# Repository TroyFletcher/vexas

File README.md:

# vexas
Vexas is a touch-type-able hardware keyboard offline Personal Organizer with a Vim-style interface, and serial support. Designed for rapid data input, data independence/security, and alarms that can be passive, persistent, or aggressive.

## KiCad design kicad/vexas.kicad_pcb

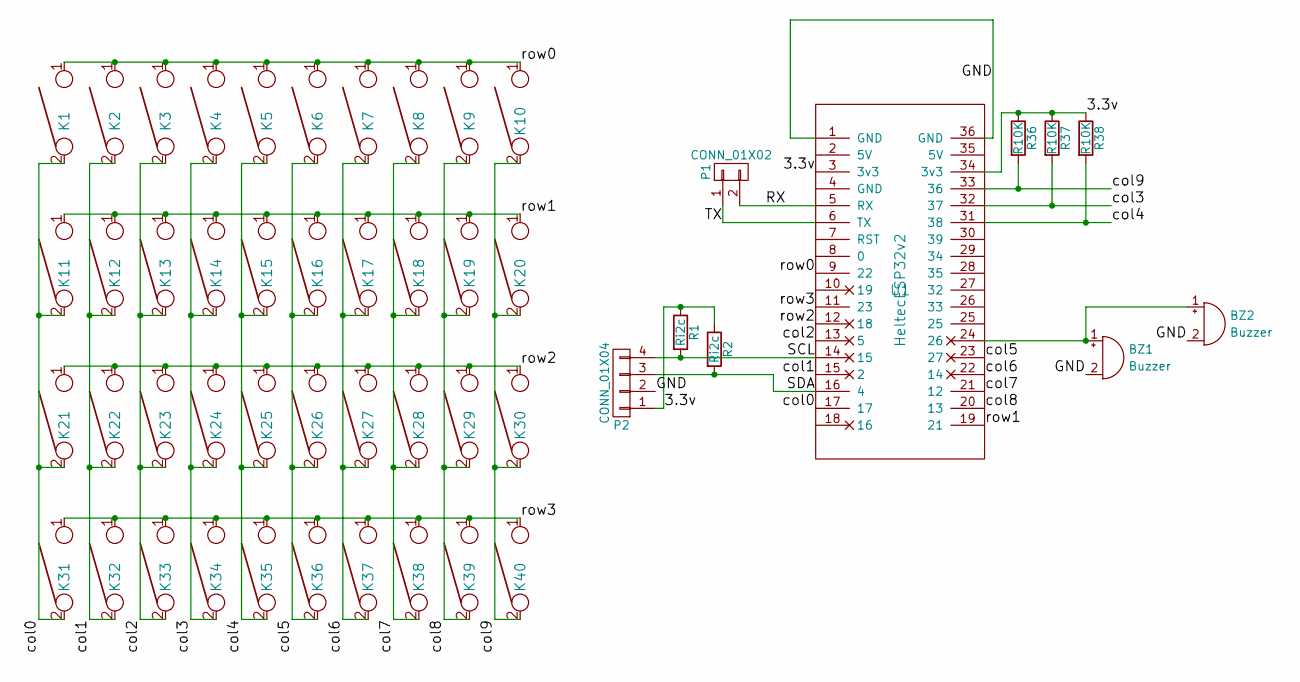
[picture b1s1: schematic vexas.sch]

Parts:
BZ1, BZ2: Buzzer; BUZZER
K1, K2, K3, K4, K5, K6, K7, K8, K9, K10, K11, K12, K13, K14, K15, K16, K17, K18, K19, K20, K21, K22, K23, K24, K25, K26, K27, K28, K29, K30, K31, K32, K33, K35, K36, K38, K39, K40: KEYSW; 6mm_mo_push_THT
K34, K37: KEYSW; 90deg6mm_mo_push_THT
P1: CONN_01X02; Pin_Header_Straight_1x02
P2: CONN_01X04; Pin_Header_Straight_1x04
R1, R2: Ri2c; R_2010_HandSoldering
R36, R37, R38: R10K; Resistor_SMD_THTuniversal_v1.0
U1: HeltecESP32v2; HeltecESP32WifiLORAv2

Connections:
/3.3v: P2.1, R1.1, R2.1, R36.1, R37.1, R38.1, U1.3 (3v3), U1.34 (3v3)
/GND: BZ1.2 (+), BZ2.2 (+), K34.3, K34.4, K37.3, K37.4, P1.3, P2.2, U1.1 (GND), U1.36 (GND)
/RX: P1.2, U1.5 (RX)
/SCL: P2.4, R1.2, U1.14 (15)
/SDA: P2.3, R2.2, U1.16 (4)
/TX: P1.1, U1.6 (TX)
/col0: K1.2, K11.2, K21.2, K31.2, U1.17
/col1: K2.2, K12.2, K22.2, K32.2, U1.15 (2)
/col2: K3.2, K13.2, K23.2, K33.2, U1.13 (5)
/col3: K4.2, K14.2, K24.2, K34.2, R37.2, U1.32 (37)
/col4: K5.2, K15.2, K25.2, K35.2, R38.2, U1.31 (38)
/col5: K6.2, K16.2, K26.2, K36.2, U1.23 (27)
/col6: K7.2, K17.2, K27.2, K37.2, U1.22 (14)
/col7: K8.2, K18.2, K28.2, K38.2, U1.21 (12)
/col8: K9.2, K19.2, K29.2, K39.2, U1.20 (13)
/col9: K10.2, K20.2, K30.2, K40.2, R36.2, U1.33 (36)
/row0: K1.1, K2.1, K3.1, K4.1, K5.1, K6.1, K7.1, K8.1, K9.1, K10.1, U1.9 (22)
/row1: K11.1, K12.1, K13.1, K14.1, K15.1, K16.1, K17.1, K18.1, K19.1, K20.1, U1.19 (21)
/row2: K21.1, K22.1, K23.1, K24.1, K25.1, K26.1, K27.1, K28.1, K29.1, K30.1, U1.12 (18)
/row3: K31.1, K32.1, K33.1, K34.1, K35.1, K36.1, K37.1, K38.1, K39.1, K40.1, U1.11 (23)
unnamed: BZ1.1 (-), BZ2.1 (-), U1.24 (26)

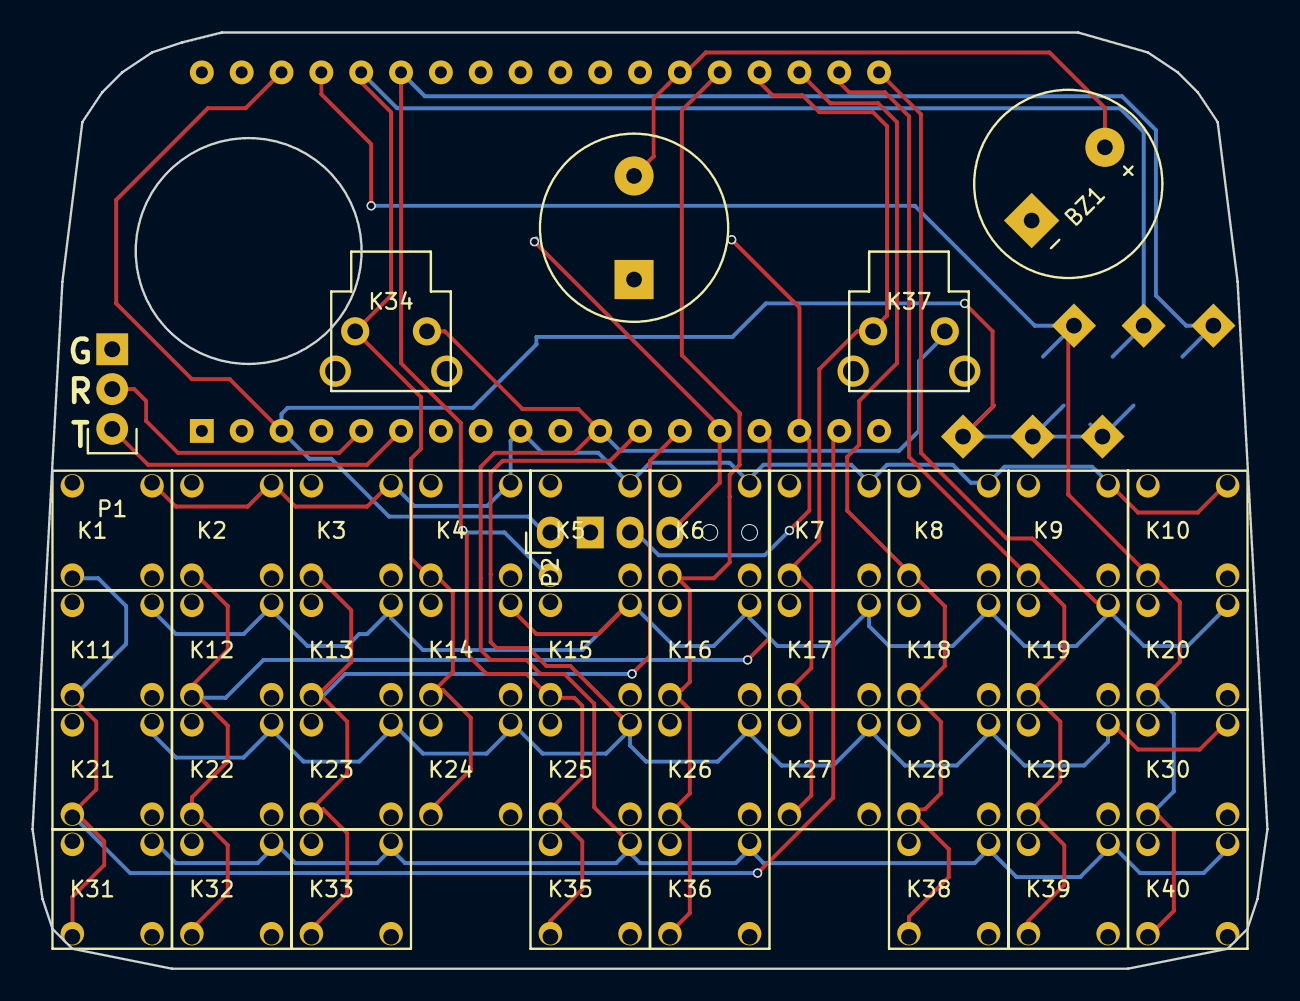
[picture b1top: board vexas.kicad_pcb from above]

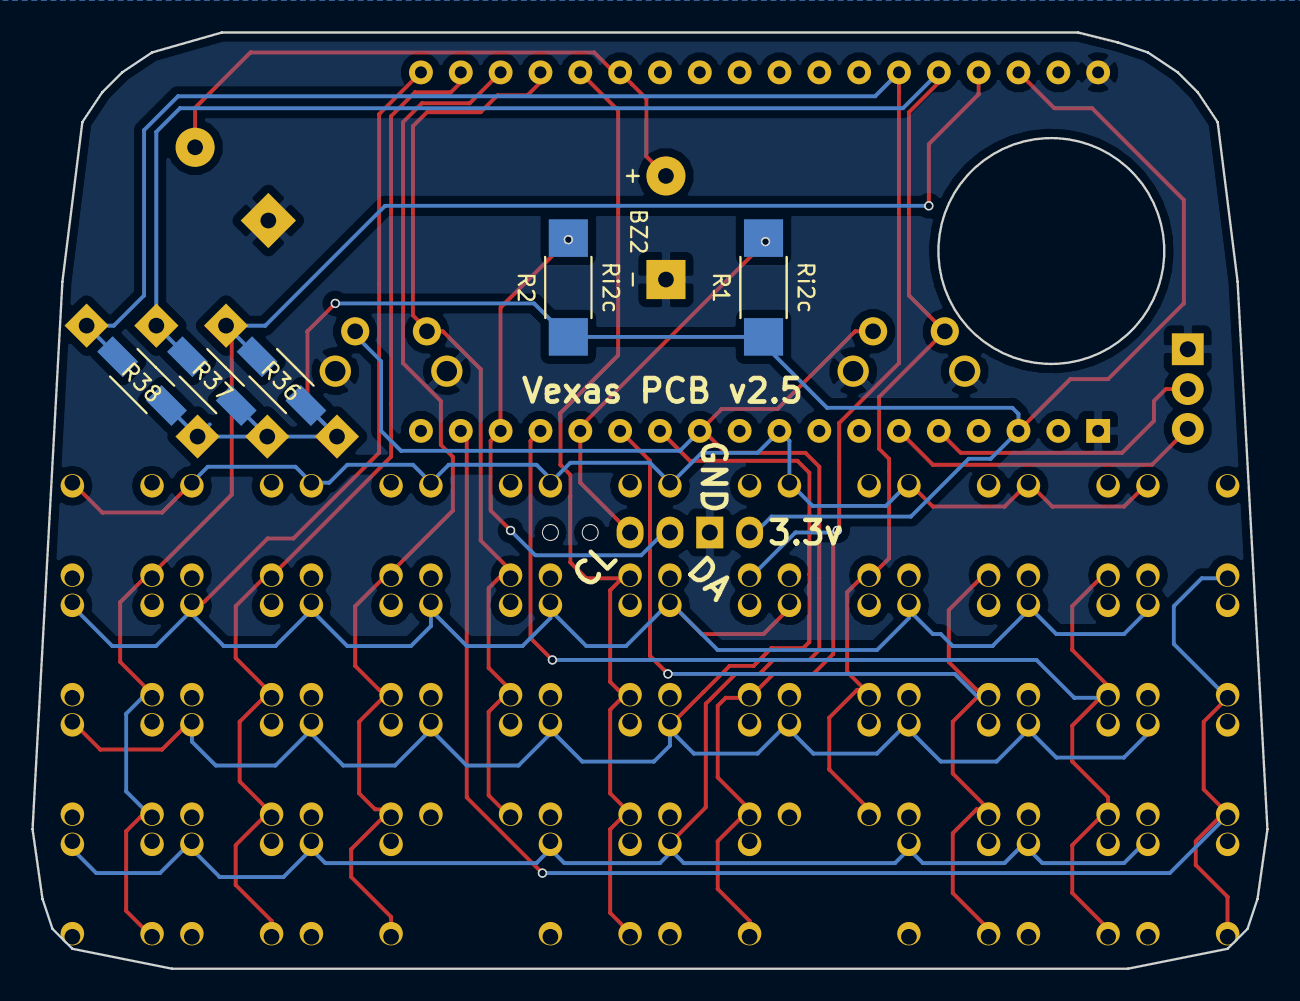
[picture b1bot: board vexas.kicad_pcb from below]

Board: 2 copper layers, 78.7 x 59.7 mm, 50 parts (2 on the bottom side), 21 nets.

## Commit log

2023-12-19 populating files
2023-12-19 added pic
